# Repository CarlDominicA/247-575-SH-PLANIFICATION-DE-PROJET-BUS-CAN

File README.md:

## Ce projet est un module CAN pour une voiture de course de type électrique

<prototype module can>
<module can>
<esp32 can>
<esp32 twai>
<esp32 projet can>
  
#### ci-dessous, une affiche pour le présentoir

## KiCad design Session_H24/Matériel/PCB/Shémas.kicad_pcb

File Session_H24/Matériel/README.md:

## Matériaux pour le produit final

##### Boitier 3D (fait sur Tinkercad)

##### Capteurs (liste des capteurs du client 0-5v)

##### Liste d'achat (liste de pièces qui n'était pas en stock) *ne contient pas toutes les pièces

##### PCB (fait sur kicad)

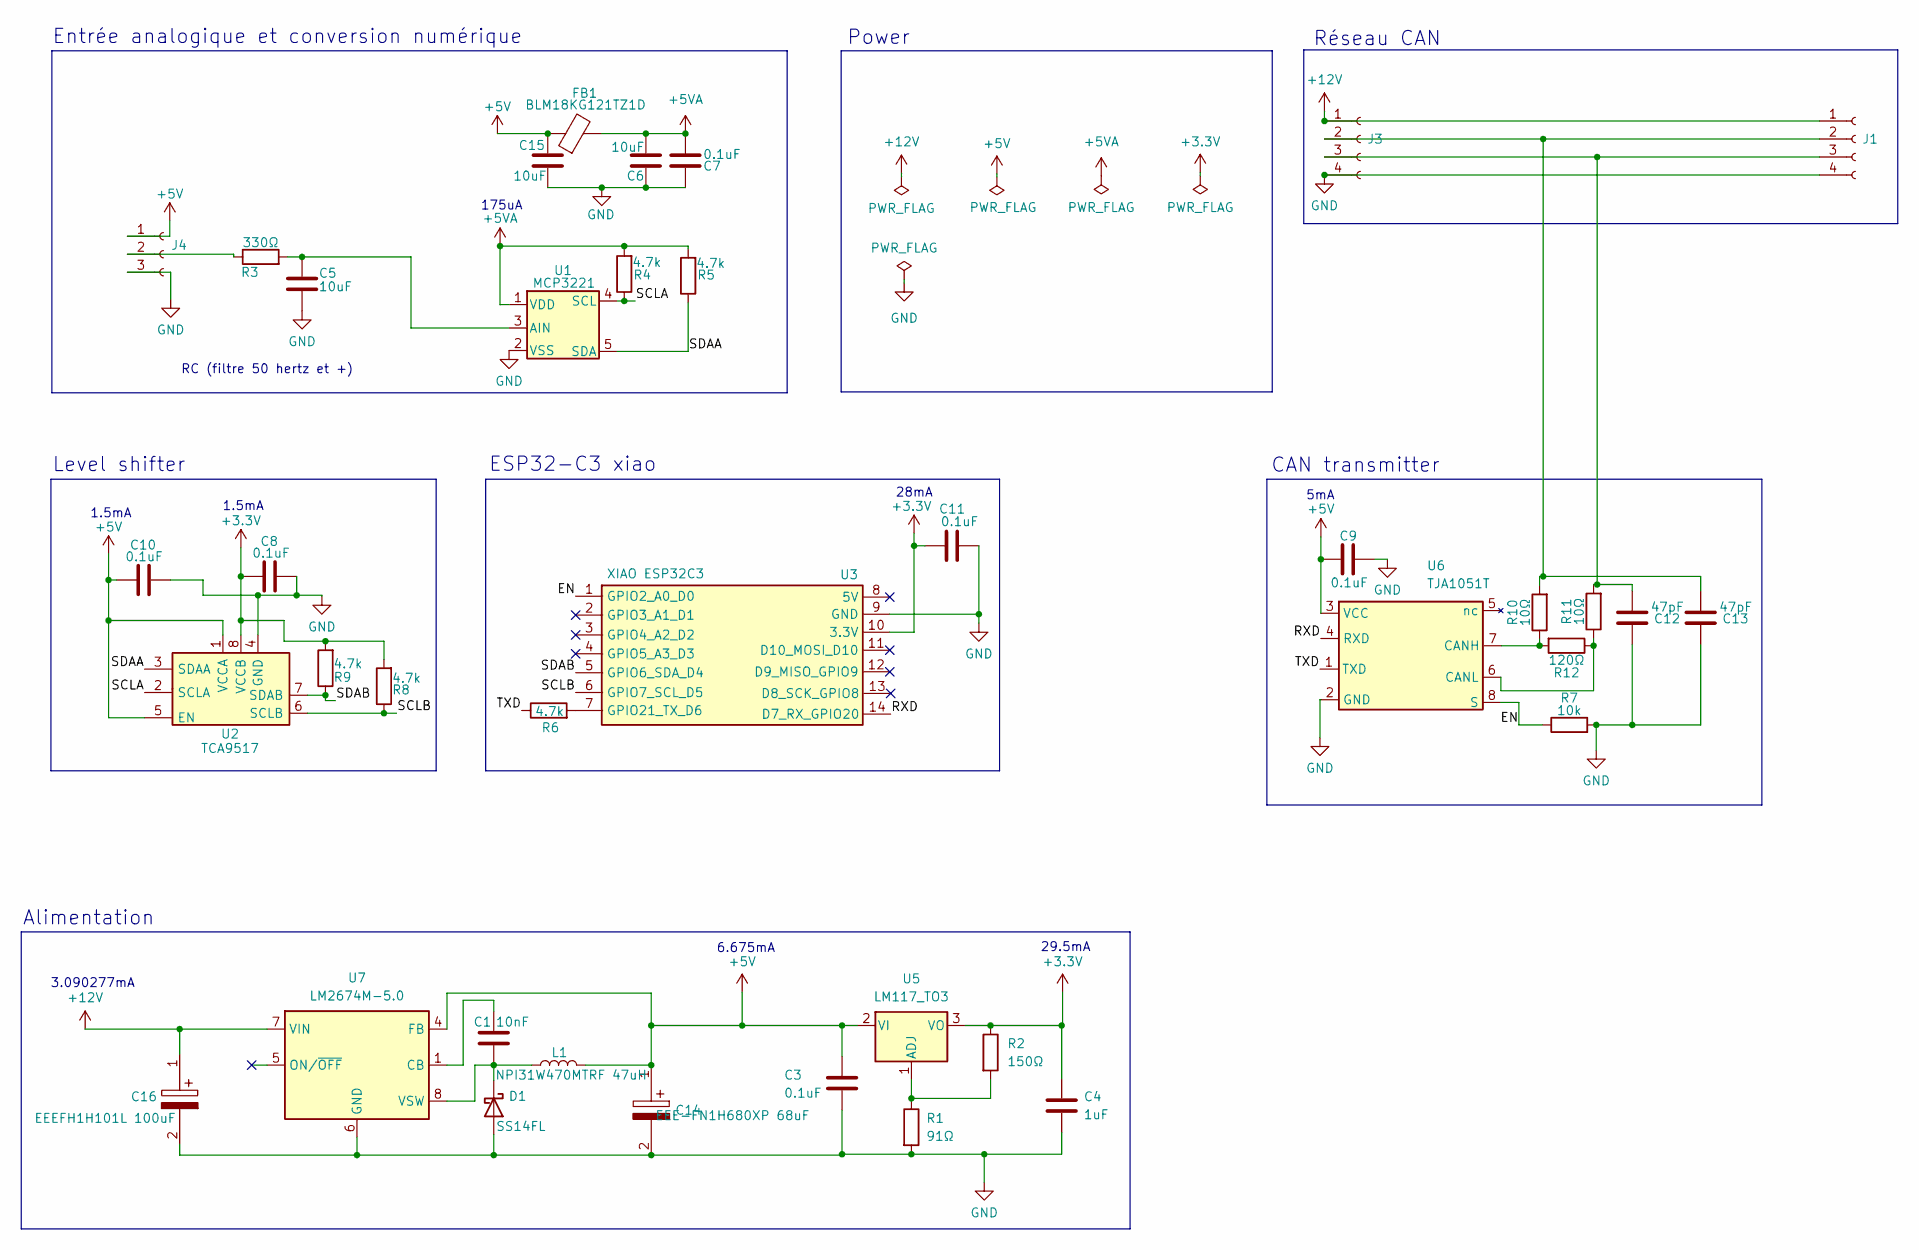
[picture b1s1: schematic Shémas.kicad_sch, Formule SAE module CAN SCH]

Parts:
C1: 10nF; C_0805_2012Metric_Pad1.18x1.45mm_HandSolder
C3, C7, C8, C9, C10, C11: 0.1uF; C_0805_2012Metric_Pad1.18x1.45mm_HandSolder
C4: 1uF; C_0805_2012Metric_Pad1.18x1.45mm_HandSolder
C5, C6, C15: 10uF; C_0805_2012Metric_Pad1.18x1.45mm_HandSolder
C12, C13: 47pF; C_0805_2012Metric_Pad1.18x1.45mm_HandSolder
C14: EEE-FN1H680XP 68uF; CP_Elec_8x6.9; Manufacturer_Part_Number EEEFH1H101L
C16: EEEFH1H101L 100uF; EEETC1V470P; Manufacturer_Part_Number EEEFH1H101L
D1: SS14FL; D_SOD-123F
FB1: BLM18KG121TZ1D; C_0603_1608Metric
J1, J3: Conn_01x04_Socket; PinSocket_1x04_P2.54mm_Vertical
J4: Conn_01x03_Socket; PinSocket_1x03_P2.54mm_Vertical
L1: NPI31W470MTRF 47uH; L_Bourns-SRR1005
R1: 91Ω; C_0805_2012Metric_Pad1.18x1.45mm_HandSolder
R2: 150Ω; C_0805_2012Metric_Pad1.18x1.45mm_HandSolder
R3: 330Ω; C_0805_2012Metric_Pad1.18x1.45mm_HandSolder
R4, R5, R6, R8, R9: 4.7k; C_0805_2012Metric_Pad1.18x1.45mm_HandSolder
R7: 10k; C_0805_2012Metric_Pad1.18x1.45mm_HandSolder
R10, R11: 10Ω; C_0805_2012Metric_Pad1.18x1.45mm_HandSolder
R12: 120Ω; C_0805_2012Metric_Pad1.18x1.45mm_HandSolder
U1: MCP3221; TSOT-23-5
U2: TCA9517; SOIC-8_3.9x4.9mm_P1.27mm
U3: XIAO ESP32C3; xiao esp32-c3
U5: LM117_TO3; SOT-223-3_TabPin2
U6: TJA1051T; SOIC-8_3.9x4.9mm_P1.27mm
U7: LM2674M-5.0; SOIC-8_3.9x4.9mm_P1.27mm

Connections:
+3.3V: C4.1, C8.2, C11.2, R2.1, R8.2, R9.2, U2.8 (VCCB), U3.10 (3.3V), U5.3 (VO)
+5V: C3.1, C9.1, C10.2, C14.1, C15.1, FB1.1, J4.1, L1.2, U2.1 (VCCA), U2.5 (EN), U5.2 (VI), U6.3 (VCC), U7.4 (FB)
+5VA: C6.2, C7.1, FB1.2, R4.2, R5.2, U1.1 (VDD)
+12V: C16.1, J1.1, J3.1, U7.7 (VIN)
/EN: R7.1, U3.1 (GPIO2_A0_D0), U6.8 (S)
/RXD: U3.14 (D7_RX_GPIO20), U6.4 (RXD)
/SCLA: R4.1, U1.4 (SCL), U2.2 (SCLA)
/SCLB: R8.1, U2.6 (SCLB), U3.6 (GPIO7_SCL_D5)
/SDAA: R5.1, U1.5 (SDA), U2.3 (SDAA)
/SDAB: R9.1, U2.7 (SDAB), U3.5 (GPIO6_SDA_D4)
/TXD: R6.1, U6.1 (TXD)
GND: C3.2, C4.2, C5.2, C6.1, C7.2, C8.1, C9.2, C10.1, C11.1, C12.1, C13.1, C14.2, C15.2, C16.2, D1.2 (A), J1.4, J3.4, J4.3, R1.2, R7.2, U1.2 (VSS), U2.4 (GND), U3.9 (GND), U6.2 (GND), U7.6 (GND)
unnamed: C1.1, D1.1 (K), L1.1, U7.8 (VSW)
unnamed: C13.2, J1.2, J3.2, R10.2
unnamed: C12.2, J1.3, J3.3, R11.2
unnamed: J4.2, R3.1
unnamed: C5.1, R3.2, U1.3 (AIN)
unnamed: R6.2, U3.7 (GPIO21_TX_D6)
unnamed: R1.1, R2.2, U5.1 (ADJ)
unnamed: R10.1, R12.2, U6.7 (CANH)
unnamed: R11.1, R12.1, U6.6 (CANL)
unnamed: C1.2, U7.1 (CB)

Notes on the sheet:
6.675mA
3.090277mA
1.5mA
Alimentation
29.5mA
Power
Entrée analogique et conversion numérique
ESP32-C3 xiao
RC (filtre 50 hertz et +)
Réseau CAN
Level shifter
28mA
CAN transmitter
5mA
175uA

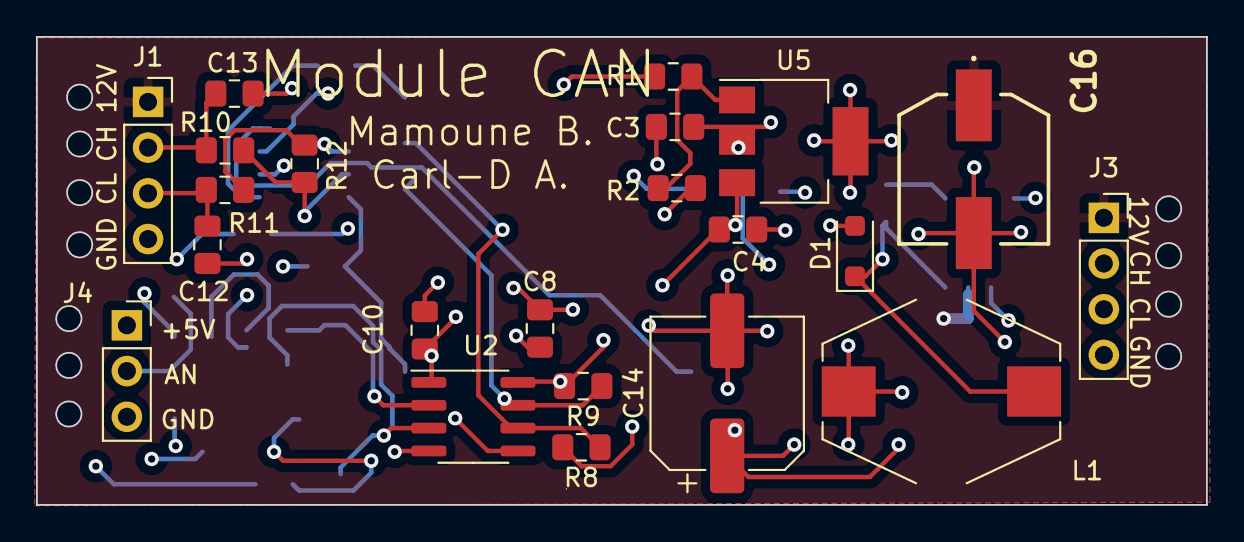
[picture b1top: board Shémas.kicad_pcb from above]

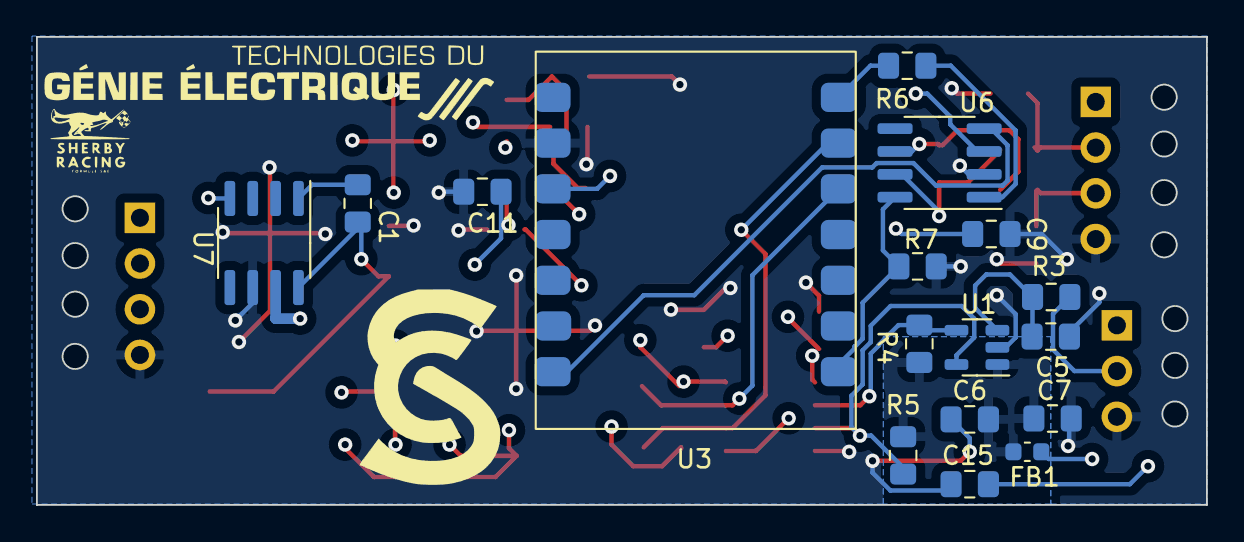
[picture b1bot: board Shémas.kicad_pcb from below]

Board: 4 copper layers, 65.0 x 26.0 mm, 39 parts (17 on the bottom side), 22 nets.

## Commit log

2024-02-16 Create Aut23
2024-03-01 1.0.1: Update main.c Transmit code
2024-03-01 1.0.1: update Esp32-C3_Sender
2024-03-01 1.0.2: Update Receive code
2024-03-01 2.0.3: Update main.cpp
2024-03-01 2.0.2: Update main.cpp
2024-03-01 2.0.3: Mise à jour fichier
    code MCP3221 fonctionnel
2024-03-01 2.0.3: Mise à jour fichier
    code de conversion ADC/ envoi message CAN fonctionnel
2024-03-01 Code réception (Test)
2024-03-01 Code Transmission (Test)
2024-03-02 2.0.4: Mise à jour
    Ajout d'un brief
2024-03-11 ajout de can receiver
    ajout de can receiver diffère de celui original
2024-03-13 Modification branches
    Changment pour fichiers
2024-03-13 tst
    test
2024-03-13 structure
    restruture du git
2024-03-13 Boitier 3D
    Ajout du boititer
2024-03-13 modification feedback Ben
2024-03-13 Mise à jour de l'entete de fichier
    Ajout de l'auteur, la date et le matériel.
2024-03-14 Update README.md
    ajout pour SEO google search
2024-03-15 Mise à jour du fichier main.cpp du dossier MCP3221
    Mise à jour de l'entête du fichier
2024-03-15 Téléversement du dossier MCP3221 2.0
    Mise à jour 2.0:
    Modification des entête de fichier
2024-03-15 Téléversement du dossier Esp32Arduino 2.0
    Suppression des fichiers en trop
2024-03-18 changement au boitier
    modification boitier 3d
2024-03-18 ok
    ok
2024-03-20 mise à jour 3.0
    Changement dans le format du message CAN à envoyer
2024-03-20 Revert "Merge branch 'main' of https://github.com/CarlDominicA/Projet_Module_CAN"
    This reverts commit 115457697176f41481bb26a3a492d3f1f2c8b880, reversing
    changes made to 382dd95bcc57aa367b2ea9962602b4170ec6f6f6.
2024-03-20 Televersement 3.0
2024-03-20 Upload 3.0
2024-03-22 mise à jour fichier
    Ajout des ID dans main.cpp
    Nettoyage fichier Esp32Arduino
2024-04-15 Mise à jour du code principale
    - changement des GPIOs pour PCB
    - changement de délai pour envoi
    - changement de board pour ESP32-C3 XIAO
2024-04-19 Mise à jour code Esp32Arduino et MCP3221
    ArduinoEsp32:
    - Ajout README.md
    - changement dans Plateformio.ini
    MCP3221:
    - ajout de README.md
2024-04-22 Mise à jour main.cpp 4.0
    - ajout de readme.md
    - changement format message CAN
    - ajout de DecimalID.h pour choix de l'ID
2024-04-22 mise à jour de README.md
2024-04-22 4.1; Mise à jour
2024-04-22 tasks.json
2024-04-24 Mise à jour 4.1
2024-04-24 Mise à jour 4.2
2024-04-26 Mise à jour 4.3
2024-04-26 Mise à jour 4.3.1
2024-05-13 Mise à jour 4.4
2024-05-27 Mise à jour 4.5
